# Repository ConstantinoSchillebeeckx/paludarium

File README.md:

:warning: this repo is no longer being worked on, the project has shifted gears to the [56gal version](https://github.com/ConstantinoSchillebeeckx/paludarium-56gal); keeping this here for historical reasons. :warning:

---

# Paludarium build
Orchid paludarium and climate control design

[Build notes](https://photoscs.wordpress.com/2016/10/26/diy-terrarium/)

## BOM

### Tank ($XX total)
- 10g aquarium ($5 craigslist)
- 4' x 2' light ceiling panel - [egg crate](https://www.google.com/shopping/product/3379815341616733842?lsf=seller:8740,store:5944499324702331793,lsfqd:0&prds=oid:14257488563428501297&q=lamp+shade&hl=en&ei=eTnxV-OXMIKFmwGgpYAQ&lsft=cm_mmc:Shopping-_-LIAs-_-D23-_-202025149&lsft=gclid:CNbavtzIvM8CFQERaQodmhcDuA) ($15 home depot)
- electric waterfall ($1 garage sale)
- [12oz great stuff foam](https://www.amazon.com/gp/product/B001AQ0FVC/ref=od_aui_detailpages00?ie=UTF8&psc=1) ($14.13 Amazon)
- [1lb. spahnum moss](https://www.amazon.com/gp/product/B00I6AJKVG/ref=od_aui_detailpages00?ie=UTF8&psc=1) ($7.99 Amazon)
- [1 x ABG mix](http://www.joshsfrogs.com/abg-mix-4-quart-1-gallon.html) ($13.98 Josh's frogs)
- [5lbs activated carbon](http://cgi.ebay.com/ws/eBayISAPI.dll?ViewItem&item=181084875793) ($9.99 ebay)
- [2lbs LECA clay](http://cgi.ebay.com/ws/eBayISAPI.dll?ViewItem&item=121695905138) ($9.45)
- [replacement pump for waterfall](http://www.newegg.com/Product/Product.aspx?Item=9SIA1GK2CA3065) ($7.99 newegg)
- [polycarbonate top 19-1/4" x 9-7/16" (1/4" thick)](http://www.tapplastics.com/product/plastics/cut_to_size_plastic/polycarbonate_sheets/516) ($13.36 TAP plastics)
- virgin cork bark
- bag of small zipties
- [PTC heater](http://www.ebay.com/itm/AC110V-100W-Electric-Ceramic-Thermostatic-Insulation-PTC-Heating-Element-Heater-/311682973018?hash=item4891c0bd5a:g:rc0AAOSwn7JYFGnt) ($10.70 ebay)

### Flora ($XX total)
- [Davallia fejeensis](https://www.glassboxtropicals.com/ProductDetails.asp?ProductCode=Davfej)

- [Ficus pumila](https://www.glassboxtropicals.com/ProductDetails.asp?ProductCode=Ficpum)

- [Ficus pumila var. minima](https://www.glassboxtropicals.com/ProductDetails.asp?ProductCode=Ficpumminima)

- [Ficus sp. 'Panama'](https://www.glassboxtropicals.com/ProductDetails.asp?ProductCode=Ficpan)

- [Marcgravia rectiflora](https://www.glassboxtropicals.com/ProductDetails.asp?ProductCode=marcrect)

- [Pyrrosia piloselloides](https://www.glassboxtropicals.com/ProductDetails.asp?ProductCode=Pyrpil)

- [Selaginella kraussiana 'Aurea'](https://www.google.com/search?q=Selaginella+kraussiana)

- [A. capillus veneris](https://www.google.com/search?q=A.+capillus+veneris)

### Controller ($XX total)
- [2 x 50cm LED bars](http://www.ebay.com/itm/12V-36-SMD-5630-50CM-0-5M-Waterproof-LED-Hard-Strip-Bar-Light-Tube-w-Cover-Cap/232100208769?_trksid=p2047675.c100623.m-1&_trkparms=aid%3D222007%26algo%3DSIC.MBE%26ao%3D1%26asc%3D38530%26meid%3Db9e91e8576b8490f9004b4baea860929%26pid%3D100623%26rk%3D1%26rkt%3D6%26sd%3D231968301261) ($4.50 ebay)
- arduino stuff
- [120mm PWM fan](http://www.newegg.com/Product/Product.aspx?Item=N82E16835494006) ($8.99 newegg)
- [temp & humidity sensor](http://www.newegg.com/Product/Product.aspx?Item=9SIABR04N71130) ($3.24 newegg)
- [ULN2003 7 Channel Darlington Driver](https://www.adafruit.com/products/970) ($1.95 Adafruit)
- [2 x 12-Channel 16-bit PWM LED Driver (TLC59711)](https://www.adafruit.com/products/1455) ($15.00 Adafruit)
- [Feather HUZZAH ESP8266](https://www.adafruit.com/products/2821) ($15.95 Adafruit)
- [Short Feather Headers](https://www.adafruit.com/products/2940) ($1.50 Adafruit)
- [UBEC DC/DC Step-Down (Buck) Converter](https://www.adafruit.com/products/1385) ($9.95 Adafruit)
- [2 x 6-conductor 0.1" socket-socket](https://www.adafruit.com/products/206) ($3.50 Adafruit)
- [Break-away 0.1" 36-pin strip right-angle male header (10 pack)](https://www.adafruit.com/products/1540) ($5.95 Adafruit)
- [4 x Servo Extension Cable](https://www.adafruit.com/products/972) ($7.80 Adafruit)
- spools of wire (1 red / 1 black)
- Schottky diode
- capacitors

### Tools
- [dremel diamond wheel point](https://www.dremel.com/en_US/products/-/show-product/accessories/7144-diamond-wheel-point) ($8.46 home depot)
- [dremel](https://www.dremel.com/en_US/products/-/show-product/tools/4000-high-performance-rotary-tool)

## Guides
- http://www.dendroboard.com/forum/members-frogs-vivariums/76255-how-build-viv-motydesign.html
- http://www.dendroboard.com/forum/members-frogs-vivariums/22002-60-gallon-construction.html
- http://www.dendroboard.com/forum/parts-construction/83431-island-paludarium-360-z-185-gal-40-x-40-x-28-a.html
- http://www.dendroboard.com/forum/parts-construction/157898-popular-helpful-parts-constructions-threads.html
- http://www.dendroboard.com/forum/parts-construction/72637-29-gallon-paludarium-build-post-i-go-details-very-pic-heavy.html#/topics/72637?page=12&_k=y1bdao

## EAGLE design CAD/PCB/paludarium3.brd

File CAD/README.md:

# Contents

**3d_print directory**
- 3d files used for printing LED holder

**PCB**
- eagle files for custom PCB

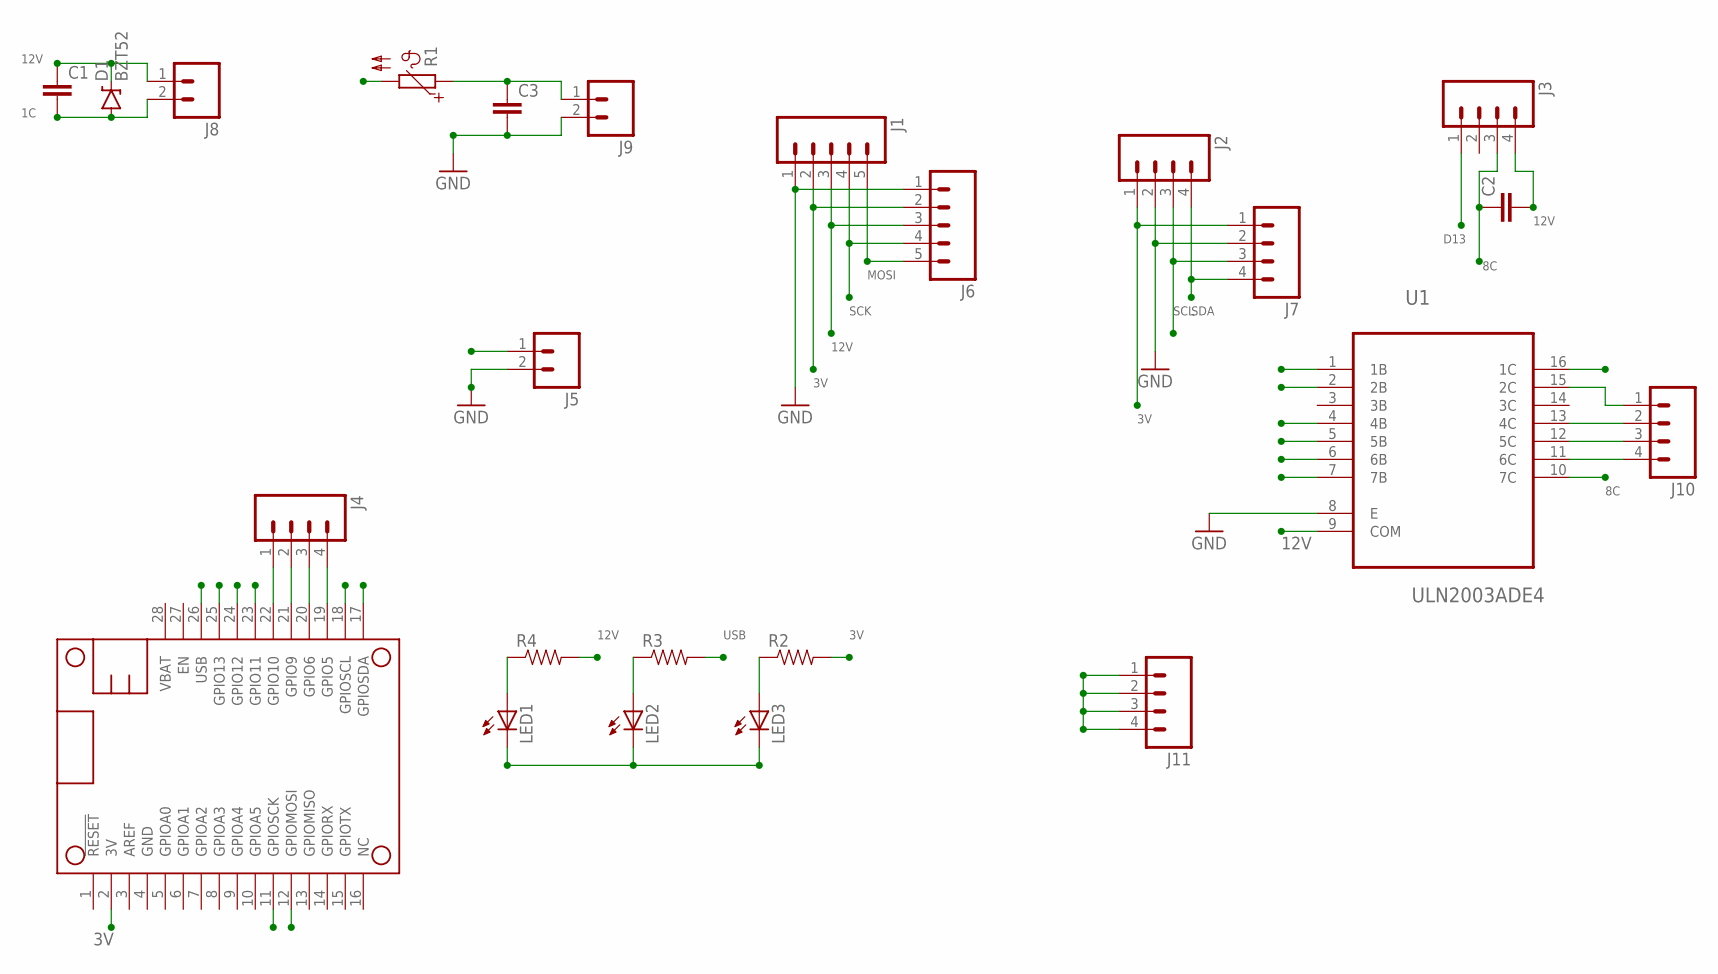
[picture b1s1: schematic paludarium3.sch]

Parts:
C1, C2, C3: C-EU025-030X050; C025-030X050
D1: BZT52; DIODE-BZT52
J1, J6: M05NO_SILK; 1X05_NO_SILK
J2, J3, J4, J7, J10, J11: M04NO_SILK_ALL_ROUND; 1X04_NO_SILK_ALL_ROUND
J5, J8, J9: M021X02_NO_SILK; 1X02_NO_SILK
LED1, LED2, LED3: LED3MM
MS1: FEATHERWING
R1: PTC679; P679
R2, R3, R4: RESISTORAXIAL-0.3; AXIAL-0.3
U1: ULN2003ADE4; SOIC127P600X175-16N

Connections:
1C: C1.2, D1.A, J8.2, U1.16 (1C)
3V: J1.2, J2.1, J6.2, J7.1, MS1.2 (3V), R2.P$2 (2)
5VIN: C3.1, J9.1, R1.1
8C: C2.1, J3.3, U1.10 (7C)
12V: C1.1, C2.2, D1.C, J1.3, J3.4, J5.1, J6.3, J8.1, J11.1, J11.2, J11.3, J11.4, R4.P$2 (2), U1.9 (COM)
D0: J4.2, MS1.21 (GPIO9), U1.4 (4B)
D2: J4.4, MS1.19 (GPIO5), U1.1 (1B)
D12: MS1.24 (GPIO12), U1.6 (6B)
D13: J3.1, MS1.23 (GPIO11)
D14: MS1.25 (GPIO13), U1.7 (7B)
D15: J4.1, MS1.22 (GPIO10), U1.5 (5B)
D16: J4.3, MS1.20 (GPIO6), U1.2 (2B)
GND: C3.2, J1.1, J2.2, J5.2, J6.1, J7.2, J9.2, LED1.K (C), LED2.K (C), LED3.K (C), MS1.4 (GND), U1.8 (E)
MOSI: J1.5, J6.5, MS1.12 (GPIOMOSI)
unnamed: J10.4, U1.11 (6C)
unnamed: J10.3, U1.12 (5C)
unnamed: J10.1, U1.15 (2C)
unnamed: LED1.A, R4.P$1 (1)
unnamed: J10.2, U1.13 (4C)
unnamed: LED3.A, R2.P$1 (1)
unnamed: LED2.A, R3.P$1 (1)
SCK: J1.4, J6.4, MS1.11 (GPIOSCK)
SCL: J2.3, J7.3, MS1.18 (GPIOSCL)
SDA: J2.4, J7.4, MS1.17 (GPIOSDA)
USB: MS1.26 (USB), R1.2, R3.P$2 (2)

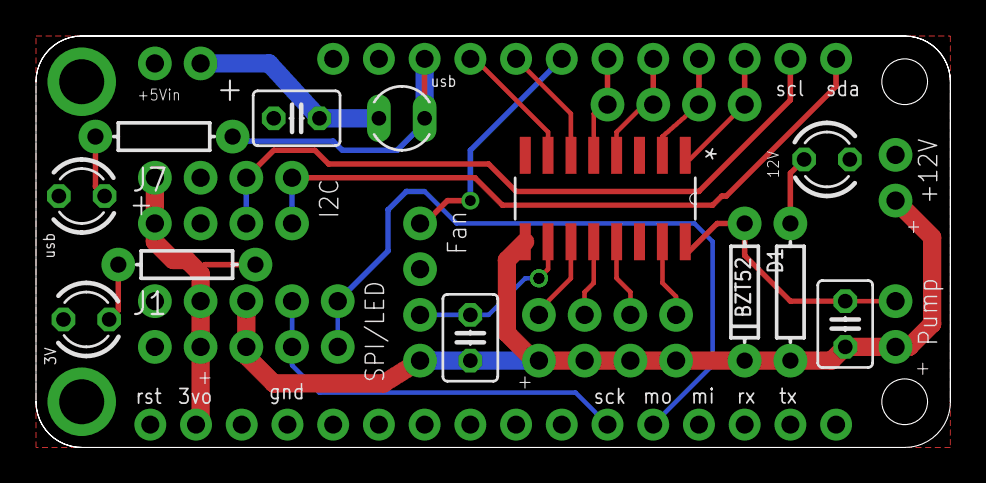
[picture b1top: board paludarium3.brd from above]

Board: 2 copper layers, 50.8 x 22.9 mm, 24 parts (0 on the bottom side), 25 nets.

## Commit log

2016-10-02 updated BOM
2016-11-03 code, figures, gitignore
2016-11-03 main code
2016-11-06 cleanup
2016-11-06 added CAD for enclosure
2016-11-06 update FAN control to ULN2803
2016-11-09 minor
2016-11-15 code cleanup

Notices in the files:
parts and their libraries:
SparkFun-Connectors: Licensing: Creative Commons ShareAlike 4.0 International - https://creativecommons.org/licenses/by-sa/4.0
